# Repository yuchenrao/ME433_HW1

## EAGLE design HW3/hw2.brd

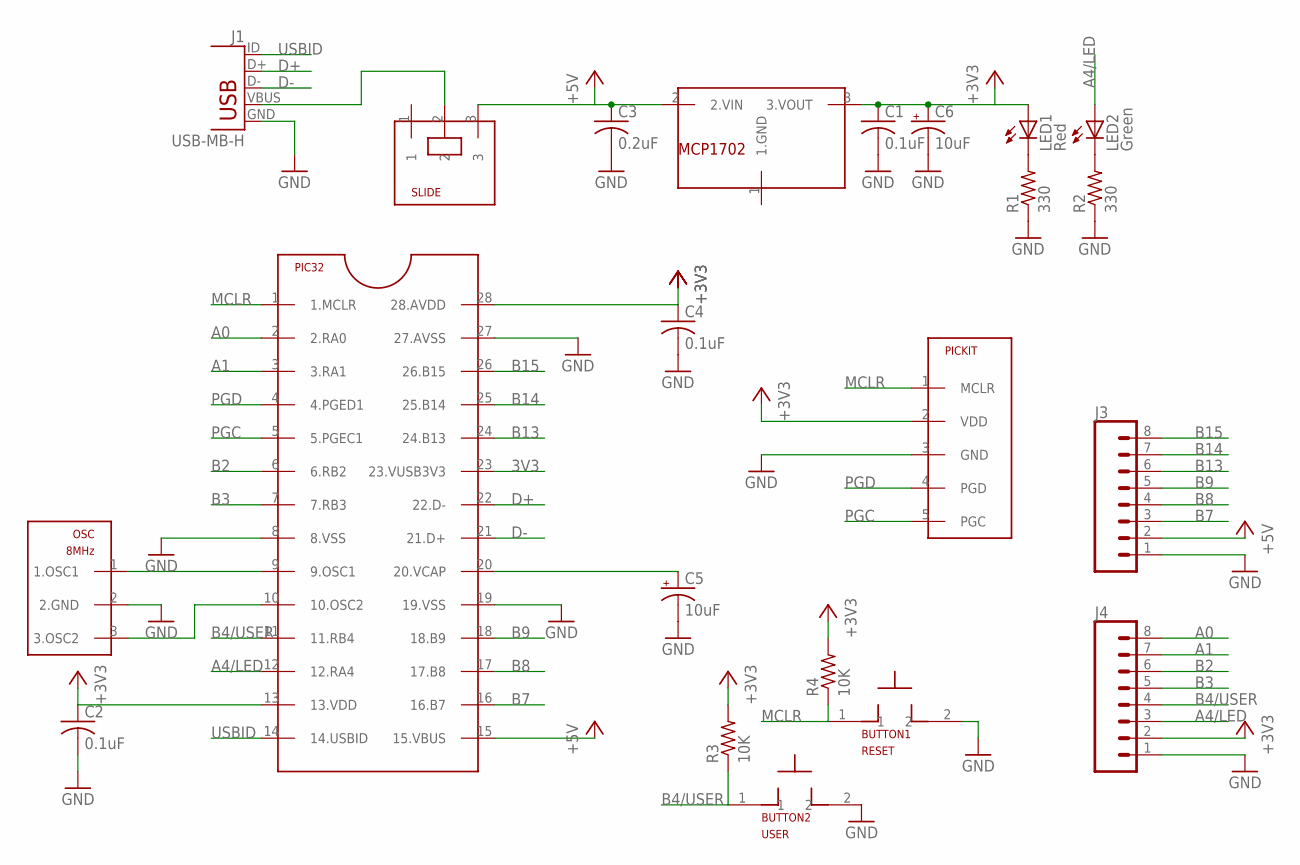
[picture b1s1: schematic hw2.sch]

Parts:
BUTTON1: RESET; PB
BUTTON2: USER; PB
C1, C2, C4: 0.1uF; C025-025X050
C3: 0.2uF; C025-025X050
C5, C6: 10uF; B45181B
J1: USB-MB-H
J3, J4: CONN_08_01; 1X08
LED1: Red; LED3MM
LED2: Green; LED3MM
MCP1702: MCP1702; TO92
OSC: 8MHz; OSC
PIC32: PIC32; DIL28-3
PICKIT: PICKIT; 1X05
R1, R2: 330; 0207/10
R3, R4: 10K; 0207/10
SLIDE: SLIDE

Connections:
3V3: PIC32.23 (23.VUSB3V3)
+3V3: C1.1, C2.1, C4.1, C6.+, J4.2, LED1.A, MCP1702.3 (3.VOUT), PIC32.13 (13.VDD), PIC32.28 (28.AVDD), PICKIT.2 (VDD), R3.2, R4.2
+5V: C3.1, J3.2, MCP1702.2 (2.VIN), PIC32.15 (15.VBUS), SLIDE.3
A0: J4.8, PIC32.2 (2.RA0)
A1: J4.7, PIC32.3 (3.RA1)
A4/LED: J4.3, LED2.A, PIC32.12 (12.RA4)
B2: J4.6, PIC32.6 (6.RB2)
B3: J4.5, PIC32.7 (7.RB3)
B4/USER: BUTTON2.1, J4.4, PIC32.11 (11.RB4), R3.1
B7: J3.3, PIC32.16 (16.B7)
B8: J3.4, PIC32.17 (17.B8)
B9: J3.5, PIC32.18 (18.B9)
B13: J3.6, PIC32.24 (24.B13)
B14: J3.7, PIC32.25 (25.B14)
B15: J3.8, PIC32.26 (26.B15)
D+: J1.D+, PIC32.22 (22.D-)
D-: J1.D-, PIC32.21 (21.D+)
GND: BUTTON1.2, BUTTON2.2, C1.2, C2.2, C3.2, C4.2, C5.-, C6.-, J1.GND, J3.1, J4.1, OSC.2 (2.GND), PIC32.8 (8.VSS), PIC32.19 (19.VSS), PIC32.27 (27.AVSS), PICKIT.3 (GND), R1.1, R2.1
MCLR: BUTTON1.1, PIC32.1 (1.MCLR), PICKIT.1 (MCLR), R4.1
unnamed: J1.VBUS, SLIDE.2
unnamed: OSC.1 (1.OSC1), PIC32.9 (9.OSC1)
unnamed: LED1.K (C), R1.2
unnamed: LED2.K (C), R2.2
unnamed: OSC.3 (3.OSC2), PIC32.10 (10.OSC2)
unnamed: C5.+, PIC32.20 (20.VCAP)
PGC: PIC32.5 (5.PGEC1), PICKIT.5 (PGC)
PGD: PIC32.4 (4.PGED1), PICKIT.4 (PGD)
USBID: J1.ID, PIC32.14 (14.USBID)

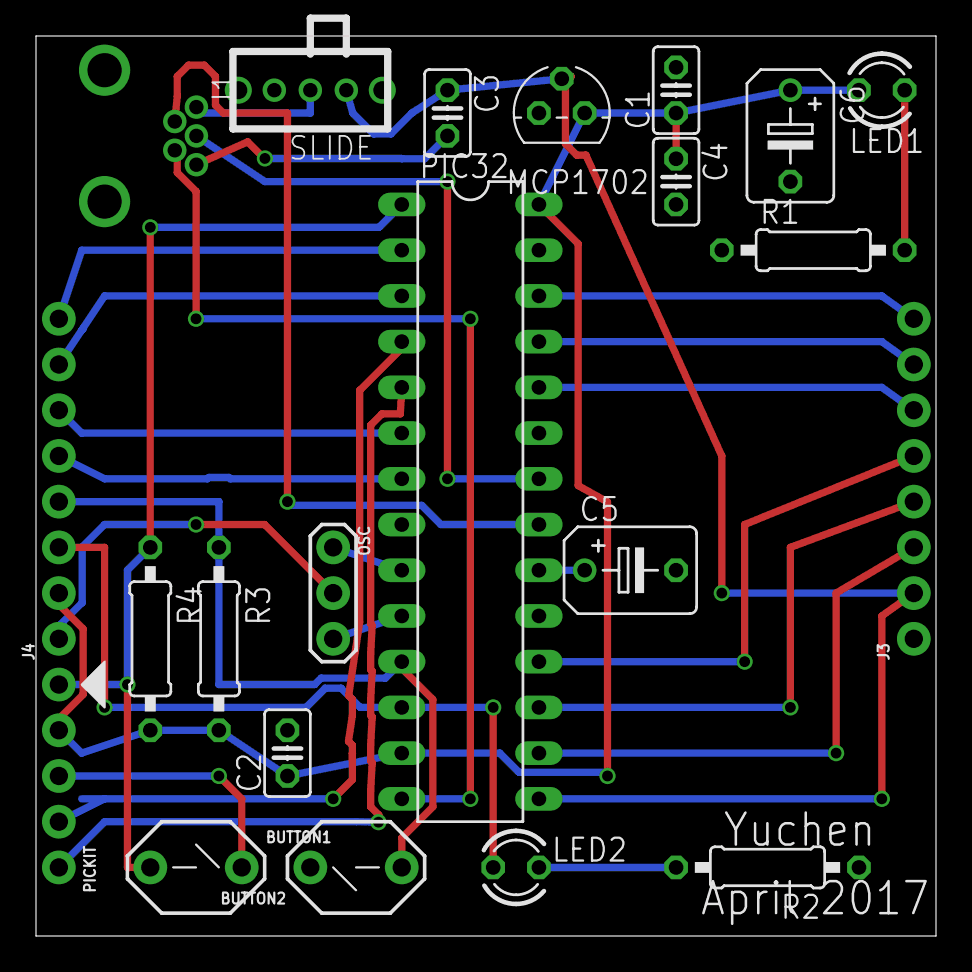
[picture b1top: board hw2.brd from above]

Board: 2 copper layers, 50.0 x 50.0 mm, 22 parts (0 on the bottom side), 27 nets.

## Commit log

2017-03-28 add a code
2017-03-29 add main
2017-03-29 final code
2017-03-29 add screenshot
2017-03-29 add breadboard picture
2017-03-29 add circuit picture
2017-03-29 add video
2017-03-30 change rideo
2017-03-30 change the folder
2017-04-05 add .lbr, .sch files
2017-04-07 finish HW3
2017-04-11 add the HW4
2017-04-11 add image
2017-04-11 fix the frequency problem
2017-04-11 change delay
2017-04-18 add HW5
2017-04-18 add circuit and demo
2017-04-18 add HW6
2017-04-19 finish hw6
2017-04-25 finish hw7
2017-04-25 add vedio
2017-04-26 add HW8
2017-04-26 add HW9
2017-04-27 finish HW9
2017-05-04 add HW10
2017-05-04 add HW11
2017-05-04 change direction
2017-05-05 add HW12
2017-05-05 add inc
2017-05-05 change
2017-05-05 add video and change FIR
2017-05-09 add HW13
2017-05-09 add demo
2017-05-11 add HW14
2017-05-12 finish HW14
2017-05-18 add wheel
2017-05-19 add board design
2017-05-19 change board3 design
2017-05-19 add real box images
2017-06-05 add hw18
2017-06-05 add hw19
2017-06-06 add final project
2017-06-06 add pic code
2017-06-07 finish HW20
2017-06-07 add cervo code
